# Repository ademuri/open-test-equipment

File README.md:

## usb-c-banana-adapter

Adapter board for a USB-C downstream-facing port (DFP). This allow supplying
power over USB-C using a lab power supply with banana jack outputs. The USB
port uses 10k pullups on the CC pins to indicate that it can supply 5V at 3A.
Note that this does **not** follow the USB-C spec - the spec requires that a
DFP only enable power on VBUS once the DFP has confirmed a device is plugged in
by reading the voltage divider on the CC channels.

## usb-c-banana-with-data

Similar to the above, but has two USB-C ports - one upstream and one downstream
port. The data lines are connected between the ports, but power is not. Power is
injected into the DFP from banana jacks. This is useful for measuring the
conducted emissions of a USB device with a DC LISN, while sending data over USB
as well.

### USB trace impedance

Given a two-layer board and the connector geometry, it's difficult to make the USB traces have the 45Ω impedance as per the USB spec. With a trace width of 0.3mm and a (best-case) spacing of 0.2mm, and a ground plane on the other side of the 1.6mm board, the impedance is around 45Ω. The traces are within 0.5mm length of each other, with a total length of ~13mm and ~14mm for the two USB pairs. This all is probably good enough, at least for full-speed USB (12Mbps).

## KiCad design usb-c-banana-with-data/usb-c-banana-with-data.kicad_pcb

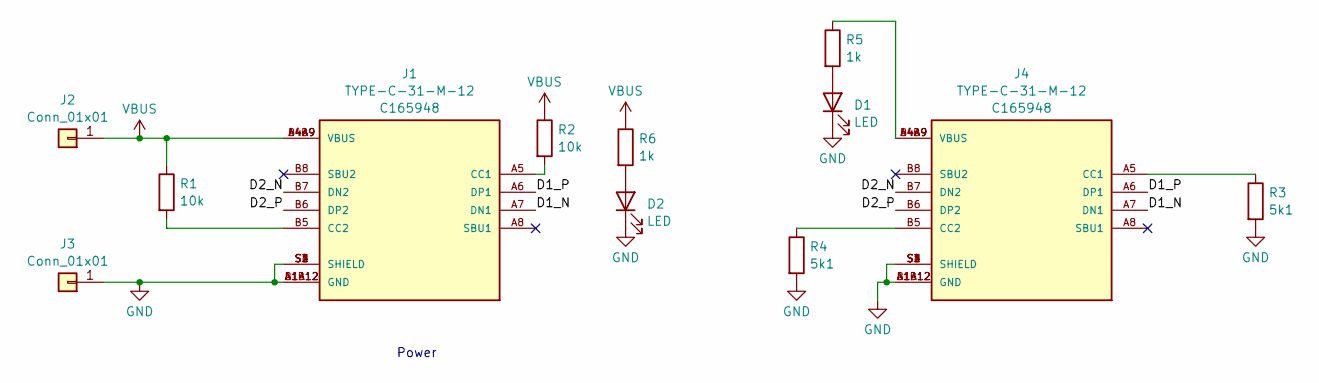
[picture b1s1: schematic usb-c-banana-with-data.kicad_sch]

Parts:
D1, D2: LED; LED_0603_1608Metric_Pad1.05x0.95mm_HandSolder; LCSC C2286
J1, J4: TYPE-C-31-M-12; HRO_TYPE-C-31-M-12; PARTREV A; LCSC C165948
J2, J3: Conn_01x01; Banana_Jack_1Pin; MPN Keystone 575-8
R1, R2: 10k; R_0603_1608Metric_Pad0.98x0.95mm_HandSolder; LCSC C25804
R3, R4: 5k1; R_0603_1608Metric_Pad0.98x0.95mm_HandSolder; LCSC C23186
R5, R6: 1k; R_0603_1608Metric_Pad0.98x0.95mm_HandSolder; LCSC C21190

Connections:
/D1_N: J1.A7 (DN1), J4.A7 (DN1)
/D1_P: J1.A6 (DP1), J4.A6 (DP1)
/D2_N: J1.B7 (DN2), J4.B7 (DN2)
/D2_P: J1.B6 (DP2), J4.B6 (DP2)
GND: D1.1 (K), D2.1 (K), J1.A1B12 (GND), J1.B1A12 (GND), J1.S1 (SHIELD), J1.S2 (SHIELD), J1.S3 (SHIELD), J1.S4 (SHIELD), J3.1, J4.A1B12 (GND), J4.B1A12 (GND), J4.S1 (SHIELD), J4.S2 (SHIELD), J4.S3 (SHIELD), J4.S4 (SHIELD), R3.2, R4.2
unnamed: D1.2 (A), R5.2
unnamed: D2.2 (A), R6.2
unnamed: J1.A5 (CC1), R2.2
unnamed: J1.B5 (CC2), R1.2
unnamed: J4.A5 (CC1), R3.1
unnamed: J4.B5 (CC2), R4.1
unnamed: J4.A4B9 (VBUS), J4.B4A9 (VBUS), R5.1
VBUS: J1.A4B9 (VBUS), J1.B4A9 (VBUS), J2.1, R1.1, R2.1, R6.1

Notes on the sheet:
Power

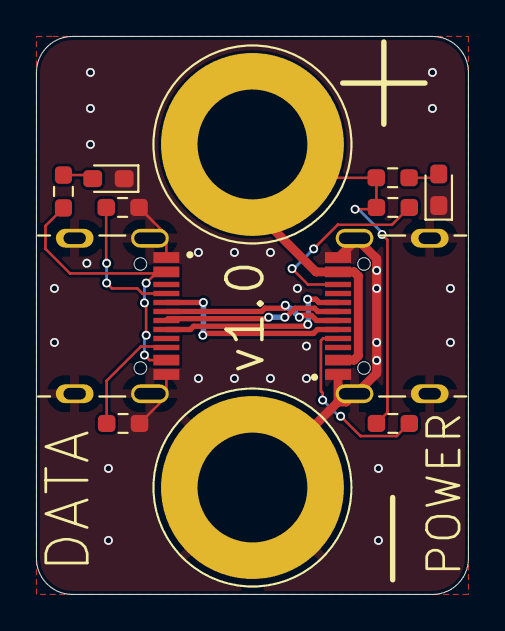
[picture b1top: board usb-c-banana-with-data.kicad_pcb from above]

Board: 2 copper layers, 24.0 x 31.0 mm, 12 parts (0 on the bottom side), 13 nets.

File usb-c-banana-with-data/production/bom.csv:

Designator,Footprint,Quantity,Value,LCSC Part #
"D1, D2",0603,2,LED,C2286
"J1, J4",HRO_TYPE-C-31-M-12,2,TYPE-C-31-M-12,C165948
"J2, J3",Banana_Jack_1Pin,2,Conn_01x01,Keystone 575-8
"R1, R2",0603,2,10k,C25804
"R3, R4",0603,2,5k1,C23186
"R5, R6",0603,2,1k,C21190

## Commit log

2024-05-30 Add gitignore for KiCAD temp files
2024-05-30 Add usb-c-banana-adapter v1.0
2024-05-30 Ignore production/backups
2024-06-27 Add contributing and license files
2025-01-07 rf-wallpaper: add basic R/Hz grid
2025-01-07 rf-wallpaper: extract math utils into a separate file
2025-01-07 rf-wallpaper: fix math to handle negative log10 units
2025-01-07 rf-wallpaper: fix resistance grid
2025-01-07 rf-wallpaper: store decade offsets as a constant
2025-01-08 rf-wallpaper: draw capacitor lines
2025-01-08 rf-wallpaper: add cap labels
2025-01-08 WIP start routing banana-with-data
2025-01-08 usb-c-banana-with-data: hardware v1.0
2025-01-08 rf-wallpaper: add minor capacitance lines
2025-01-08 rf-wallpaper: add inductance lines and fix clipping
2025-01-08 rf-wallpaper: rename inner variables to avoid shadowing
2025-01-08 rf-wallpaper: rename variables hz -> f
2025-01-08 rf-wallpaper: add highlight modes
2025-01-09 rf-wallpaper: add minor highlighting for frequency
2025-01-09 rf-wallpaper: add minor highlighting for resistance
2025-01-09 rf-wallpaper: simplify drawCapacitanceLines
2025-01-09 Simplify inductance lines to use one outer loop
2025-01-09 rf-wallpaper: simplify capacitance lines to use a single loop
2025-01-09 rf-wallpaper: display frequency and resistance values
2025-01-09 rf-wallpaper: display 2 decimal places for value display
2025-01-09 rf-wallpaper: extract mouse C and R into functions
2025-01-09 rf-wallpaper: add capacitance and inductance value display
2025-01-09 rf-wallpaper: improve sig fig handling
2025-01-09 Add capacitance highlighting
2025-01-09 rf-wallpaper: add inductance highlighting
2025-01-10 Add docs folder for gh pages
2025-01-10 Rename rf-wallpaper.html -> index.html
2025-01-10 Add test index.html
2025-01-11 Move index.html to root
2025-01-11 Migrate to React: just dump the p5js code into a single component
2025-01-11 rf-wallpaper: Migrate to non-deprecated P5 wrapper
2025-01-11 rf-wallpaper: allow using typescript
2025-01-11 Enable typescript checking
2025-01-11 rf-wallpaper: get typescript working and fix errors and lint
2025-01-11 rf-wallpaper: add proof-of-concept for frequency display in React
2025-01-11 rf-wallpaper: extract math into its own module
2025-01-11 rf-wallpaper: re-add math unit tests
2025-01-11 rf-wallpaper: forget dist/
2025-01-11 rf-wallpaper: display all values
2025-01-11 rf-wallpaper: enable eslint
2025-01-11 rf-wallpaper: fix eslint for React
2025-01-11 Configure Prettier and format everything
2025-01-11 rf-wallpaper: install eslint-config-prettier
2025-01-11 rf-wallpaper: fix app test
2025-01-12 rf-wallpaper: allow selecting frequency highlight mode
2025-01-12 rf-wallpaper: add All highlight logic
2025-01-12 Remove rf-wallpaper. Moved to separate repo.
